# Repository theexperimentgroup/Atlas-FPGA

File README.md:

# PROYECTO ATLAS

La placa ATLAS se diseña con el objetivo de crear un multicore basado en SBC (SINGLE BOARD COMPUTER).

Inicialmente la placa adaptadora ATLAS es un proyecto para la placa CYC1000 y la SBC Raspberry Pi.

Mas info y fotos en este [hilo](http://www.forofpga.es/viewtopic.php?f=28&t=376&p=1548#p1548), en su propio [foro](http://www.forofpga.es/viewforum.php?f=240&sid=bd3e070f65599ff111ad0494e4459535) de foroFPGA, en [telegram](https://t.me/CYC1000) o [discord](https://discord.gg/YDdmtwh).

Licensed under Cern OHL
http://ohwr.org/cernohl

### Guía rápida

Si ya tienes tu CYC1000, una raspberry Pi, y la placa ATLAS (la puedes conseguir en el grupo de [telegram](https://t.me/CYC1000)), sigue esta guía rápida para empezar a trastear. 

El proyecto está empezando y se irán simplificando los pasos en el futuro de forma que para cargar los cores ya no será necesario acceder al terminal de Linux de la placa SBC.

#### Ensamblaje de las placas:

Leyenda: (1) Placa Atlas, (2) FPGA CYC1000, (3) SBC Raspberry Pi, (4) Alimentación general, (5) DB9 para joystick, (6) teclado PS2, (7) ratón PS2, (8) salida video HDMI, (9) jack 3.5 audio, (10) tarjeta microSD ATLAS, (11) tarjeta microSD rPi

Otras conexiones opcionales: 

(12) Conexiones de vídeo y teclado a la SBC rPi para acceder al terminal de linux . No es necesario si has configurado acceso ssh por WiFi.

(13) USB Blaster para cargar cores directamente a la CYC1000. No es necesario si la carga se hace a través de la SBC rPi.

#### Configuración inicial de la SBC raspberry Pi

* Descarga raspberry Pi OS Lite https://www.raspberrypi.org/software/operating-systems/ y grábalo en una tarjeta micro SD
* Arranca  la SBC con la tarjeta micro SD del paso anterior en el zócalo (11) (no es necesario tenerla conectada aún a la placa ATLAS) con el video y teclado conectados y con un cargador de adecuado amperaje (>2A). 
  * Para acceder al terminal Linux de la rPI el usuario / contraseña por defecto son: pi / raspberry
* Configuración de la raspberry Pi con el comando `sudo raspi-config` (la configuración del WiFi es opcional y puedes encontrar mas información [aquí](https://www.raspberrypi.org/documentation/configuration/wireless/wireless-cli.md)): 
  * 5 Localization Options
    * L4 WLAN country 
    * L3 keyboard
  * 1 system options
    * S1 wireless LAN

#### Instalación del cargador de cores programRBF en la FPGA 

Nota: vamos a trabajar desde el directorio /home/pi que es el que aparece por defecto al arrancar el terminal Linux con el usuario "pi".

* Instala la librería WiringPi:

  ```
  wget https://project-downloads.drogon.net/wiringpi-latest.deb
  sudo dpkg -i wiringpi-latest.deb
  ```

* Compila el ejecutable para cargar los cores:

  ```
  wget https://raw.githubusercontent.com/shaeon/programrbf/main/programrbf_v01.cpp
  g++ programrbf_v01.cpp -lwiringPi -o programrbf
  ```

#### Arranca los cores desde el terminal Linux de la SBC

* Copia los cores con extensión .rbf a la tarjeta SD, en la partición "rootfs", directorio ""/home/pi".

* Carga el core con el ejecutable programrbf (el ejemplo carga el [msx_multicore2.rbf](./cores/msx_multicore2.rbf) de MSX1):

  ```
  ./programrbf msx_multicore2.rbf 17 22 4 27
  ```
  
  Nota: El core [msx_multicore2.rbf](./cores/msx_multicore2.rbf) de MSX1 requiere soldar un reloj adicional de 50 MHz, y tener una tarjeta micro SD con [este contenido](https://mega.nz/file/20pi1aiY#FwhOZryEUyuyU1gEUCVma1ndn-2BqtvH7RUx-qwgqs0) insertada en el zócalo micro SD (10) de la placa ATLAS.

#### Script para cargar un core automáticamente al arrancar la SBC

* Ejecuta los siguientes comandos en el terminal de Línux:

  ```sh
  crontab -e
  #selecciona por ejemplo nano y al final del fichero cron añade lo siguiente:
  @reboot ~/programrbf msx_multicore2.rbf 17 22 4 27
  ```

### **Reloj adicional de 50 Mhz:**

La placa CYC1000 dispone de un reloj de 12 Mhz. Algunos cores necesitan de un reloj adicional de 50 MHz a soldar en el espacio que se ve en la siguiente [foto](http://www.forofpga.es/viewtopic.php?f=240&t=390).

Dónde conseguir el reloj:

* [Arrow](https://www.arrow.com/en/products/ecs-2520mv-500-bn-tr/ecs-international?q=ECS-2520MV-500-BN-TR)

Listado de cores que van a 50 MHz:

* MSX1

### **Colaboraciones:**

Se necesita la [colaboración](https://github.com/SoCFPGA-learning/General/tree/main/Github_ayuda) para poder incrementar los recursos disponibles para la comunidad entorno esta placa de desarrollo.    

### Comunidad:

* [Telegram group](https://t.me/CYC1000) 
* [Discord channel](https://discord.gg/YDdmtwh)

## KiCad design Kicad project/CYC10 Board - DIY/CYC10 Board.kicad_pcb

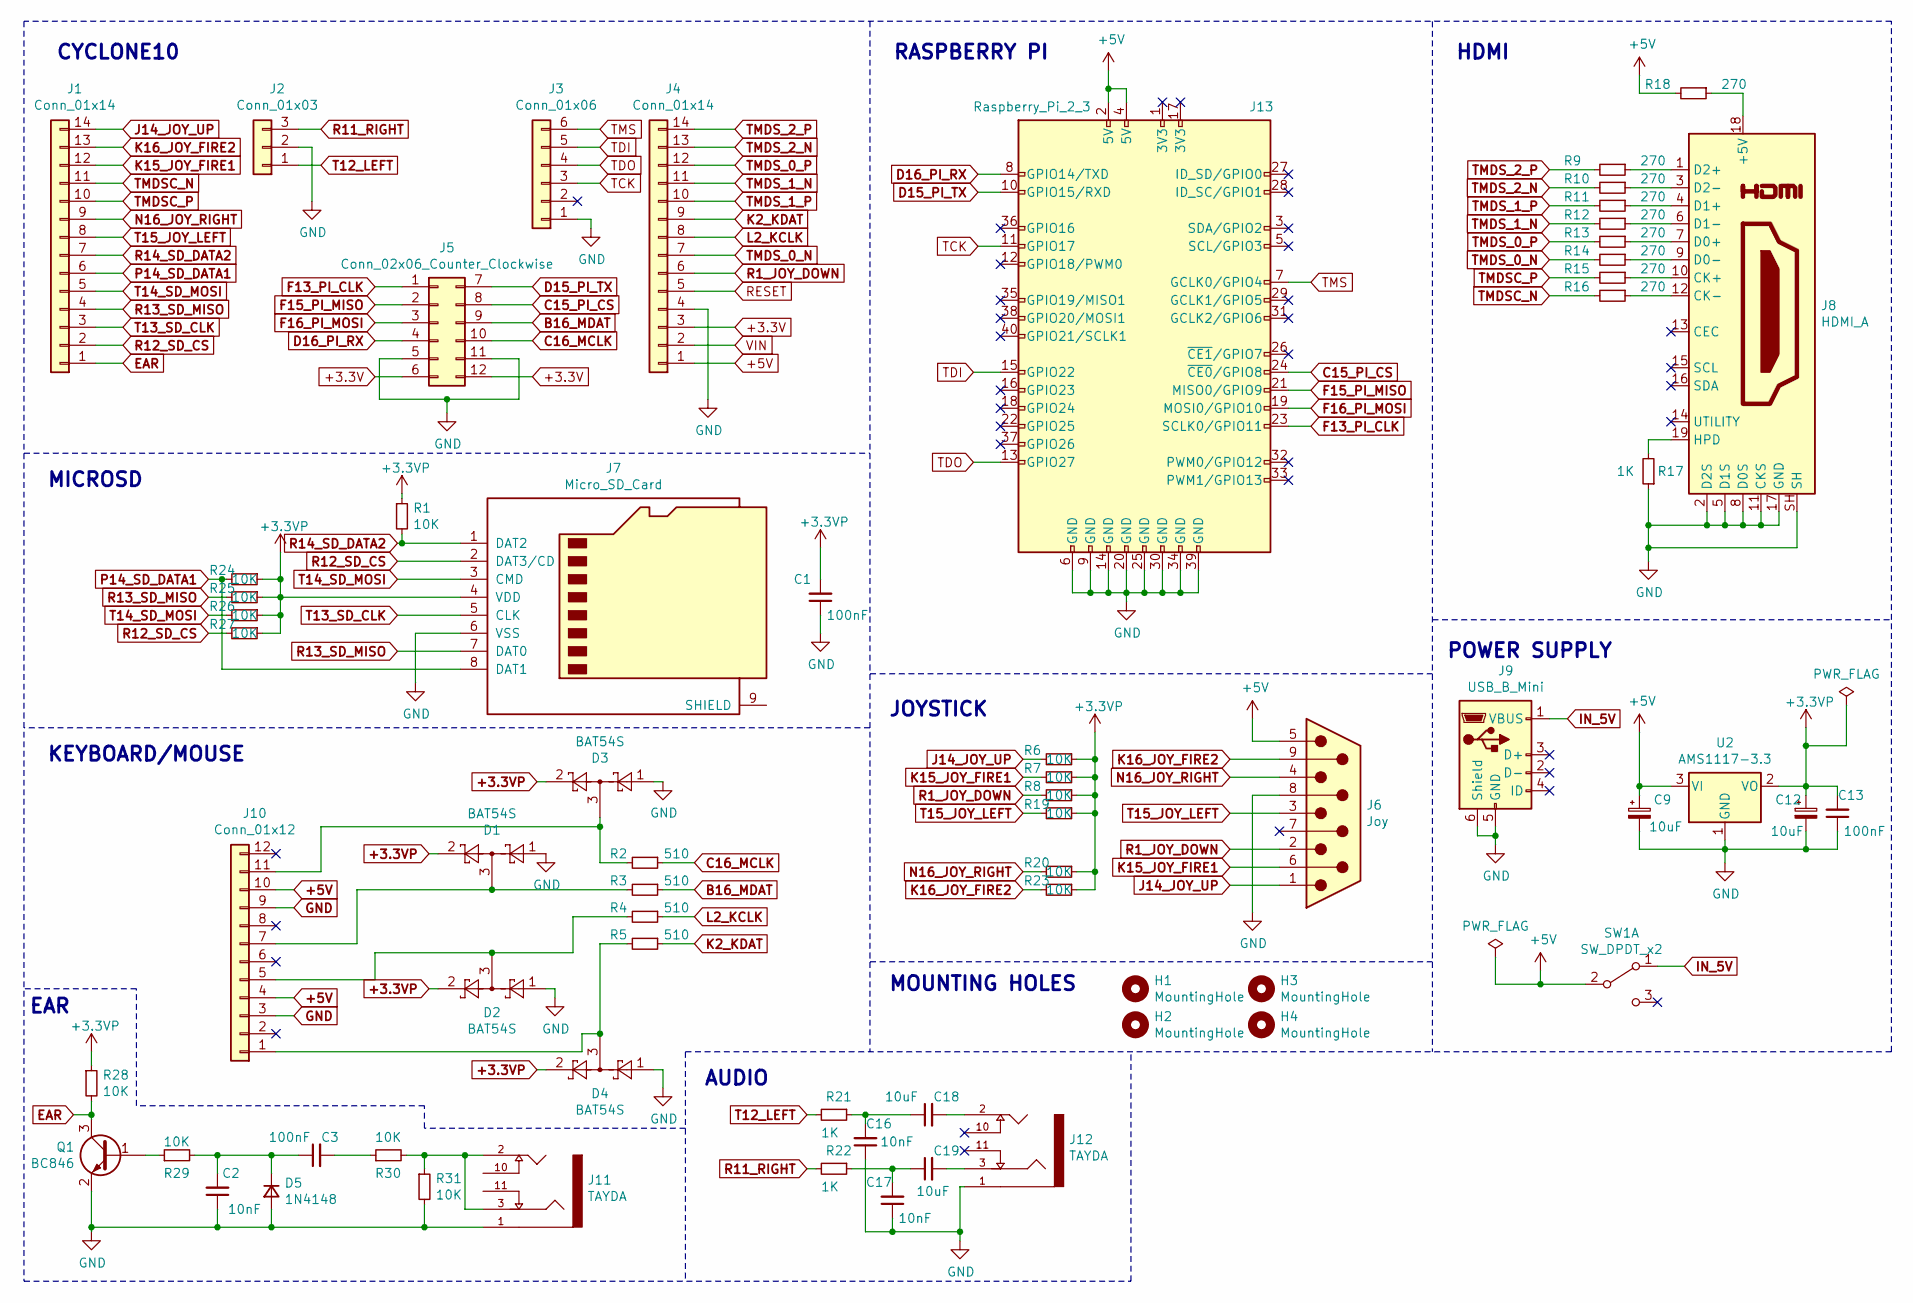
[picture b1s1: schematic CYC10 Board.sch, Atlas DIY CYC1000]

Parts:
C1, C3, C13: 100nF; C_0805_2012Metric
C2, C16, C17: 10nF; C_0805_2012Metric
C9, C12, C18, C19: 10uF; C_0805_2012Metric
D1, D2, D3, D4: BAT54S; SOT-23
D5: 1N4148; D_MiniMELF
H1, H2, H3, H4: MountingHole; MountingHole_3.2mm_M3
J1, J4: Conn_01x14; PinHeader_1x14_P2.54mm_Vertical
J2: Conn_01x03; PinHeader_1x03_P2.54mm_Vertical
J3: Conn_01x06; PinHeader_1x06_P2.54mm_Vertical
J5: Conn_02x06_Counter_Clockwise; PMOD
J6: Joy; DSUB-9_Male_Horizontal_P2.77x2.84mm_EdgePinOffset9.90mm_Hou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
J7: Micro_SD_Card; Conn_uSDcard1
J8: HDMI_A; HDMI_BIEN
J9: USB_B_Mini; USB_Mini-B_Wuerth_65100516121_Horizontal
J10: Conn_01x12; PS2_DOBLE
J11, J12: TAYDA; Tayda_Audio_Bien
J13: Raspberry_Pi_2_3; Conector_PI
Q1: BC846; SOT-23
R1, R6, R7, R8, R19, R20, R23, R24, R25, R26, R27, R28, R29, R30, R31: 10K; R_0805_2012Metric
R2, R3, R4, R5: 510; R_0805_2012Metric
R9, R10, R11, R12, R13, R14, R15, R16, R18: 270; R_0805_2012Metric
R17, R21, R22: 1K; R_0805_2012Metric
SW1: SW_DPDT_x2; Switch
U2: AMS1117-3.3; SOT-223-3_TabPin2

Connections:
+3.3V: J4.3, J5.6, J5.12
+3.3VP: C1.2, C12.1, C13.2, D1.2, D2.2, D3.2, D4.2, J7.4 (VDD), R1.1, R6.1, R7.1, R8.1, R19.1, R20.1, R23.1, R24.1, R25.1, R26.1, R27.1, R28.1, U2.2 (VO)
+5V: C9.1, J4.1, J6.5, J10.4, J10.10, J13.2 (5V), J13.4 (5V), R18.2, SW1.2 (B), U2.3 (VI)
B16_MDAT: J5.9, R3.1
C15_PI_CS: J5.8, J13.24 (~CE0~/GPIO8)
C16_MCLK: J5.10, R2.1
D15_PI_TX: J5.7, J13.10 (GPIO15/RXD)
D16_PI_RX: J5.4, J13.8 (GPIO14/TXD)
EAR: J1.1, Q1.3 (C), R28.2
F13_PI_CLK: J5.1, J13.23 (SCLK0/GPIO11)
F15_PI_MISO: J5.2, J13.21 (MISO0/GPIO9)
F16_PI_MOSI: J5.3, J13.19 (MOSI0/GPIO10)
GND: C1.1, C2.1, C9.2, C12.2, C13.1, C16.1, C17.1, D1.1, D2.1, D3.1, D4.1, D5.2 (A), J2.2, J3.1, J4.4, J5.5, J5.11, J6.8, J7.6 (VSS), J8.2 (D2S), J8.5 (D1S), J8.8 (D0S), J8.11 (CKS), J8.17 (GND), J8.SH, J9.5 (GND), J9.6 (Shield), J10.3, J10.9, J11.1, J12.1, J13.6 (GND), J13.9 (GND), J13.14 (GND), J13.20 (GND), J13.25 (GND), J13.30 (GND), J13.34 (GND), J13.39 (GND), Q1.2 (E), R17.1, R31.2, U2.1 (GND)
IN_5V: J9.1 (VBUS), SW1.1 (A)
J14_JOY_UP: J1.14, J6.1, R6.2
K2_KDAT: J4.9, R5.1
K15_JOY_FIRE1: J1.12, J6.6, R7.2
K16_JOY_FIRE2: J1.13, J6.9, R23.2
L2_KCLK: J4.8, R4.1
N16_JOY_RIGHT: J1.9, J6.4, R20.2
unnamed: C2.2, C3.1, D5.1 (K), R29.2
unnamed: C3.2, R30.1
unnamed: C16.2, C18.1, R21.1
unnamed: C17.2, C19.1, R22.1
unnamed: C18.2, J12.2
unnamed: C19.2, J12.3
unnamed: D1.3, J10.7, R3.2
unnamed: D2.3, J10.5, R4.2
unnamed: D3.3, J10.11, R2.2
unnamed: D4.3, J10.1, R5.2
unnamed: J8.1 (D2+), R9.1
unnamed: J8.3 (D2-), R10.1
unnamed: J8.4 (D1+), R11.1
unnamed: J8.6 (D1-), R12.1
unnamed: J8.7 (D0+), R13.1
unnamed: J8.9 (D0-), R14.1
unnamed: J8.10 (CK+), R15.1
unnamed: J8.12 (CK-), R16.1
unnamed: J8.18 (+5V), R18.1
unnamed: J8.19 (HPD), R17.2
unnamed: J11.2, J11.3, R30.2, R31.1
unnamed: Q1.1 (B), R29.1
P14_SD_DATA1: J1.6, J7.8 (DAT1), R24.2
R1_JOY_DOWN: J4.6, J6.2, R8.2
R11_RIGHT: J2.3, R22.2
R12_SD_CS: J1.2, J7.2 (DAT3/CD), R27.2
R13_SD_MISO: J1.4, J7.7 (DAT0), R25.2
R14_SD_DATA2: J1.7, J7.1 (DAT2), R1.2
RESET: J4.5
T12_LEFT: J2.1, R21.2
T13_SD_CLK: J1.3, J7.5 (CLK)
T14_SD_MOSI: J1.5, J7.3 (CMD), R26.2
T15_JOY_LEFT: J1.8, J6.3, R19.2
TCK: J3.3, J13.11 (GPIO17)
TDI: J3.5, J13.15 (GPIO22)
TDO: J3.4, J13.13 (GPIO27)
TMDSC_N: J1.11, R16.2
TMDSC_P: J1.10, R15.2
TMDS_0_N: J4.7, R14.2
TMDS_0_P: J4.12, R13.2
TMDS_1_N: J4.11, R12.2
TMDS_1_P: J4.10, R11.2
TMDS_2_N: J4.13, R10.2
TMDS_2_P: J4.14, R9.2
TMS: J3.6, J13.7 (GCLK0/GPIO4)
VIN: J4.2

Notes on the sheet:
JOYSTICK
POWER SUPPLY
AUDIO
KEYBOARD/MOUSE
MICROSD
CYCLONE10
RASPBERRY PI
HDMI
MOUNTING HOLES
EAR

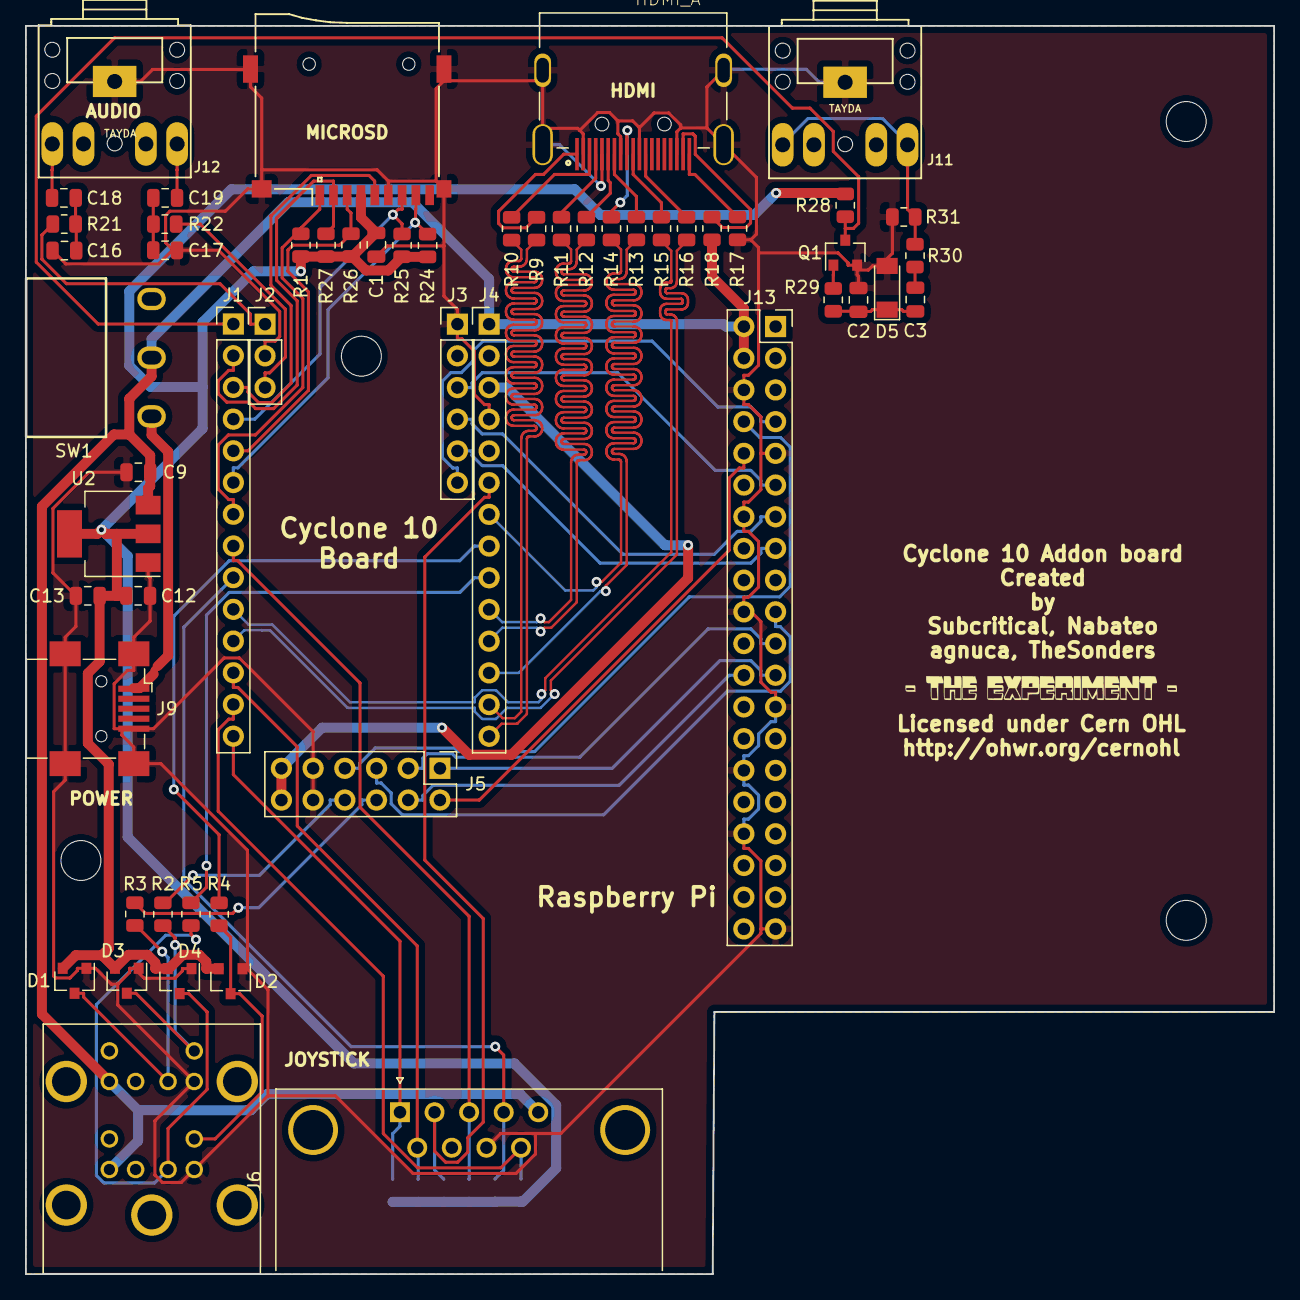
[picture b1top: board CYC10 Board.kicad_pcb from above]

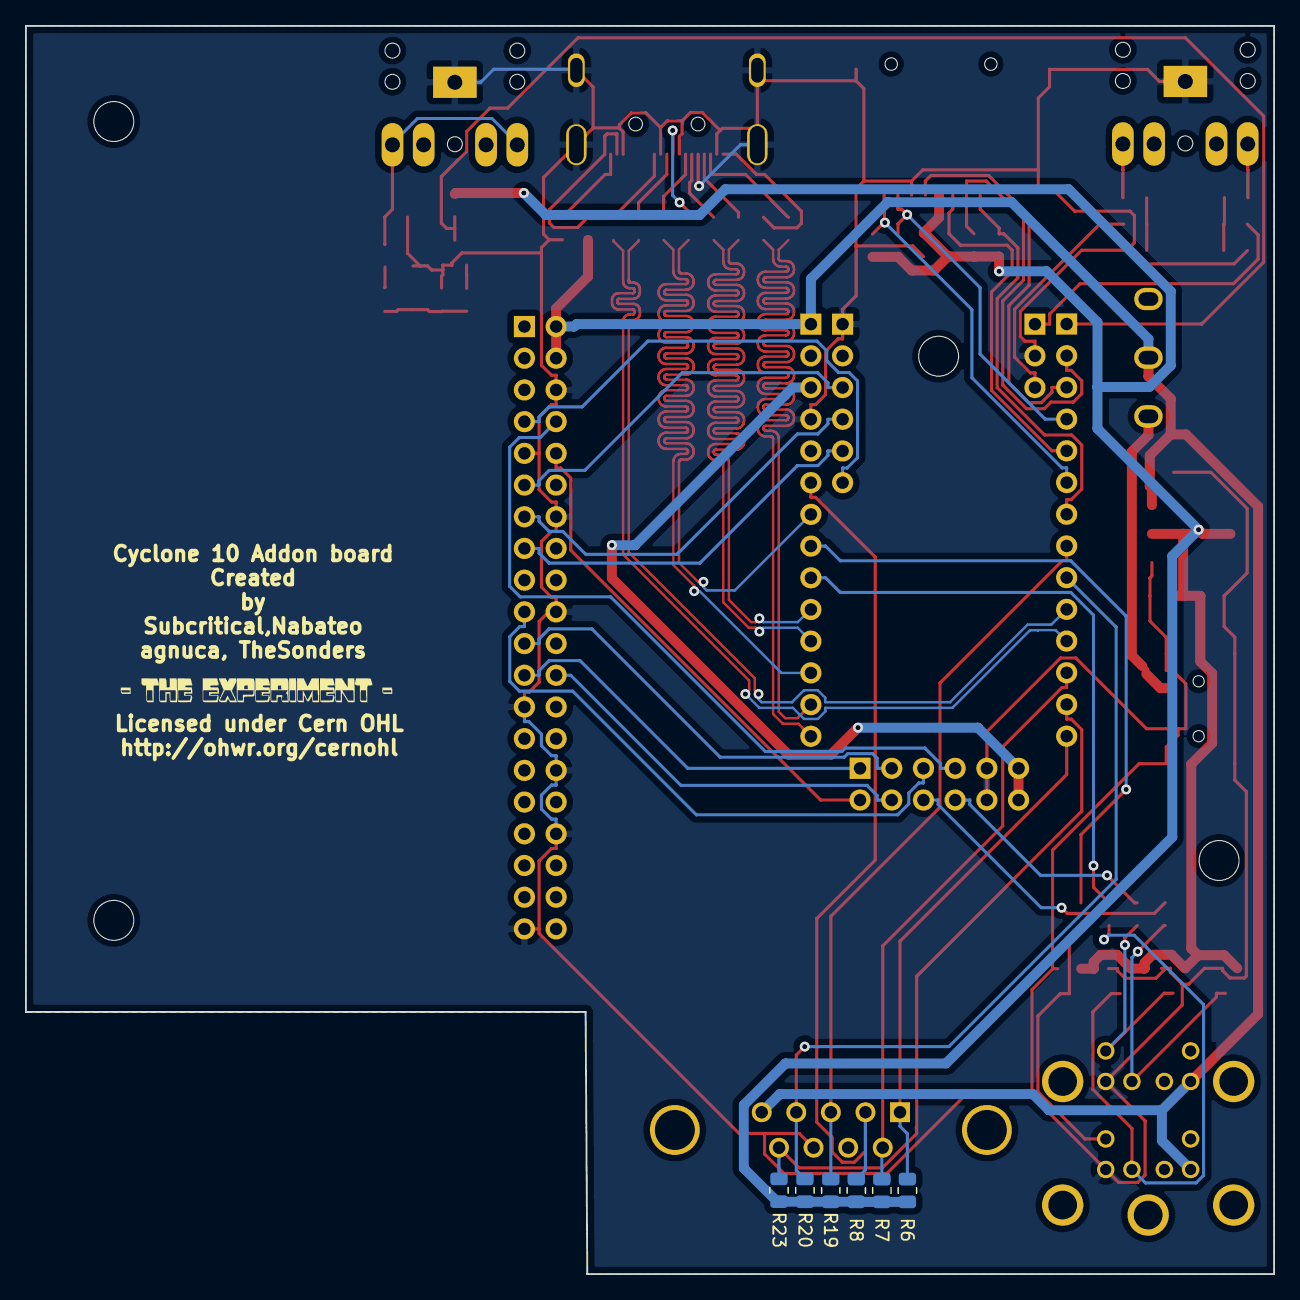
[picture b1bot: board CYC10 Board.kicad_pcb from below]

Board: 2 copper layers, 100.0 x 100.0 mm, 66 parts (6 on the bottom side), 64 nets.
